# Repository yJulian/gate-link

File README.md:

# Gate Link

ESP32-S3 firmware for a two-leaf gate controller, exposed to [Home Assistant](https://www.home-assistant.io/) over MQTT with [MQTT Discovery](https://www.home-assistant.io/integrations/mqtt/#mqtt-discovery). No manual YAML entity setup needed.

`no_std` Rust on the [Embassy](https://embassy.dev/) async executor (via `esp-rtos`), targeting `xtensa-esp32s3-none-elf`.

## Features

- Open / close / stop, plus impulse control (local push button and radio
  remote) with the classic open → stop → close → stop → open press cycle
- Two independent light barriers: one stops the gate outright, the other
  only blocks closing
- Wind guard (anemometer) input that force-opens and locks the gate until
  explicitly reset (dedicated input or an MQTT button)
- Light barrier bypass (MQTT switch or local input) for faulty barriers:
  the next open/close movement ignores both barriers, then it turns itself
  off again
- Warning light that blinks while the gate moves and while the bypass is on
- Gate leaf position and wind-lock state persisted to flash, so a power
  loss doesn't lose track of where the gate was
- First-boot provisioning: the device opens its own Wi-Fi hotspot with an
  HTTP form to collect Wi-Fi + MQTT settings — no hardcoded credentials

## Hardware / wiring

GPIO assignments and input polarity are hardcoded in the wiring section at
the top of `main()` in `src/bin/main.rs`; leaf timing lives in
`src/physical/gate_config.rs`. Default pinout (ESP32-S3-DevKitC-1):

| Signal                        | GPIO |
|-------------------------------|------|
| BOOT button (config reset)    | 0    |
| Leaf A: open / close relay    | 15 / 16 |
| Leaf B: open / close relay    | 17 / 18 |
| Warning light (`LAMP_BLINK`)  | 21   |
| IN1 local push button         | 7    |
| IN2 radio remote              | 8    |
| IN3 wind sensor (anemometer)  | 9    |
| IN4 wind lock reset           | 10   |
| IN5 light barrier 1           | 11   |
| IN6 light barrier 2           | 12   |
| IN7 light barrier bypass      | 13   |

All inputs are active-low with an internal pull-up. Each leaf runs 15s per
direction by default, with leaf A opening first and leaf B closing first.

## Building

The toolchain is pinned via `rust-toolchain.toml` to the `esp` channel,
installed with [`espup`](https://github.com/esp-rs/espup). The target
(`xtensa-esp32s3-none-elf`) and `build-std` are already configured in
`.cargo/config.toml`, so no extra flags are needed:

```sh
cargo build --release              # what CI builds
cargo fmt --all -- --check
cargo clippy --all-features --workspace -- -D warnings
cargo test-core                    # host unit tests (gate-core, app-core, MQTT client)
cargo run                          # builds, flashes and opens a serial monitor via espflash
```

## First boot / provisioning

1. On first boot (or after a config reset), the device has no stored Wi-Fi
   credentials and opens an open (passwordless) hotspot named
   `mqtt-gate-setup` at `192.168.2.1`.
2. Connect to it and open `http://192.168.2.1/` to fill in the Wi-Fi SSID/
   password and MQTT broker host/port/credentials.
3. Submitting the form persists the config to flash and reboots the device
   into station mode, where it joins your Wi-Fi and connects to the broker.
4. To reprovision, hold the onboard **BOOT** button (GPIO0) for 5 seconds
   during boot — this erases the stored config and drops back into
   provisioning mode.

## Home Assistant integration

On connecting to the broker, the device publishes retained MQTT Discovery
configs for four entities:

| Entity                                               | Type          | Notes                                              |
|------------------------------------------------------|---------------|----------------------------------------------------|
| Gate (`mqtt_gate_cover`)                             | Cover         | open / close / stop, reports position              |
| Wind Monitor Input (`mqtt_gate_wind`)                | Binary sensor | on while the wind lock is engaged                  |
| Light Barrier Bypass (`mqtt_gate_barrier_bypass`)    | Switch        | ignore the light barriers for the next movement    |
| Reset Windmonitor (`mqtt_gate_reset_anemometer`)     | Button        | clears the wind lock                               |

No manual entity configuration in Home Assistant is required — they appear
automatically once the device connects.

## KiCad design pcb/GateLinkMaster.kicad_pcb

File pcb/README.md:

# GateLink PCB

KiCad hardware design for **GateLink Master**, the carrier board that hosts
an ESP32-DevKitC module and drives the two-leaf gate's four relays. This is
the board the [firmware](../README.md) runs on.

## What's on the board

- **U3** — ESP32-DevKitC module (socketed, not soldered directly)
- **K2–K5** — four SPDT relays (SANYOU SRD series, Form C), each switched
  through a transistor driver (Q2–Q5) with a flyback diode
- **J1** — 5-pin screw terminal for digital inputs (push button, radio
  remote, wind sensor, light barriers — see the firmware's input wiring)
- **J2–J5** — 3-pin screw terminals, one per relay (NO / COM / NC)
- **J6** — 2-pin screw terminal for 24V power input

Four relays map to the firmware's two motors: one open + one close relay
per gate leaf.

## Files

- `GateLinkMaster.kicad_pro` / `.kicad_sch` / `.kicad_pcb` — the KiCad
  project, schematic and board layout
- `fp-lib-table` / `sym-lib-table` — project-local footprint/symbol library
  tables (relative paths, so the project is self-contained if opened from
  this folder)
- `GateLinkMaster-backups/` — KiCad's automatic timestamped backups, kept
  out of the repo's diff history but versioned as zip snapshots
- `LICENSE` — GPLv3, applies to the hardware design files in this folder

## Opening the project

Requires [KiCad](https://www.kicad.org/) (developed against KiCad 9/10).
Open `GateLinkMaster.kicad_pro`; schematic and PCB editors will pick up the
project-local library tables automatically.

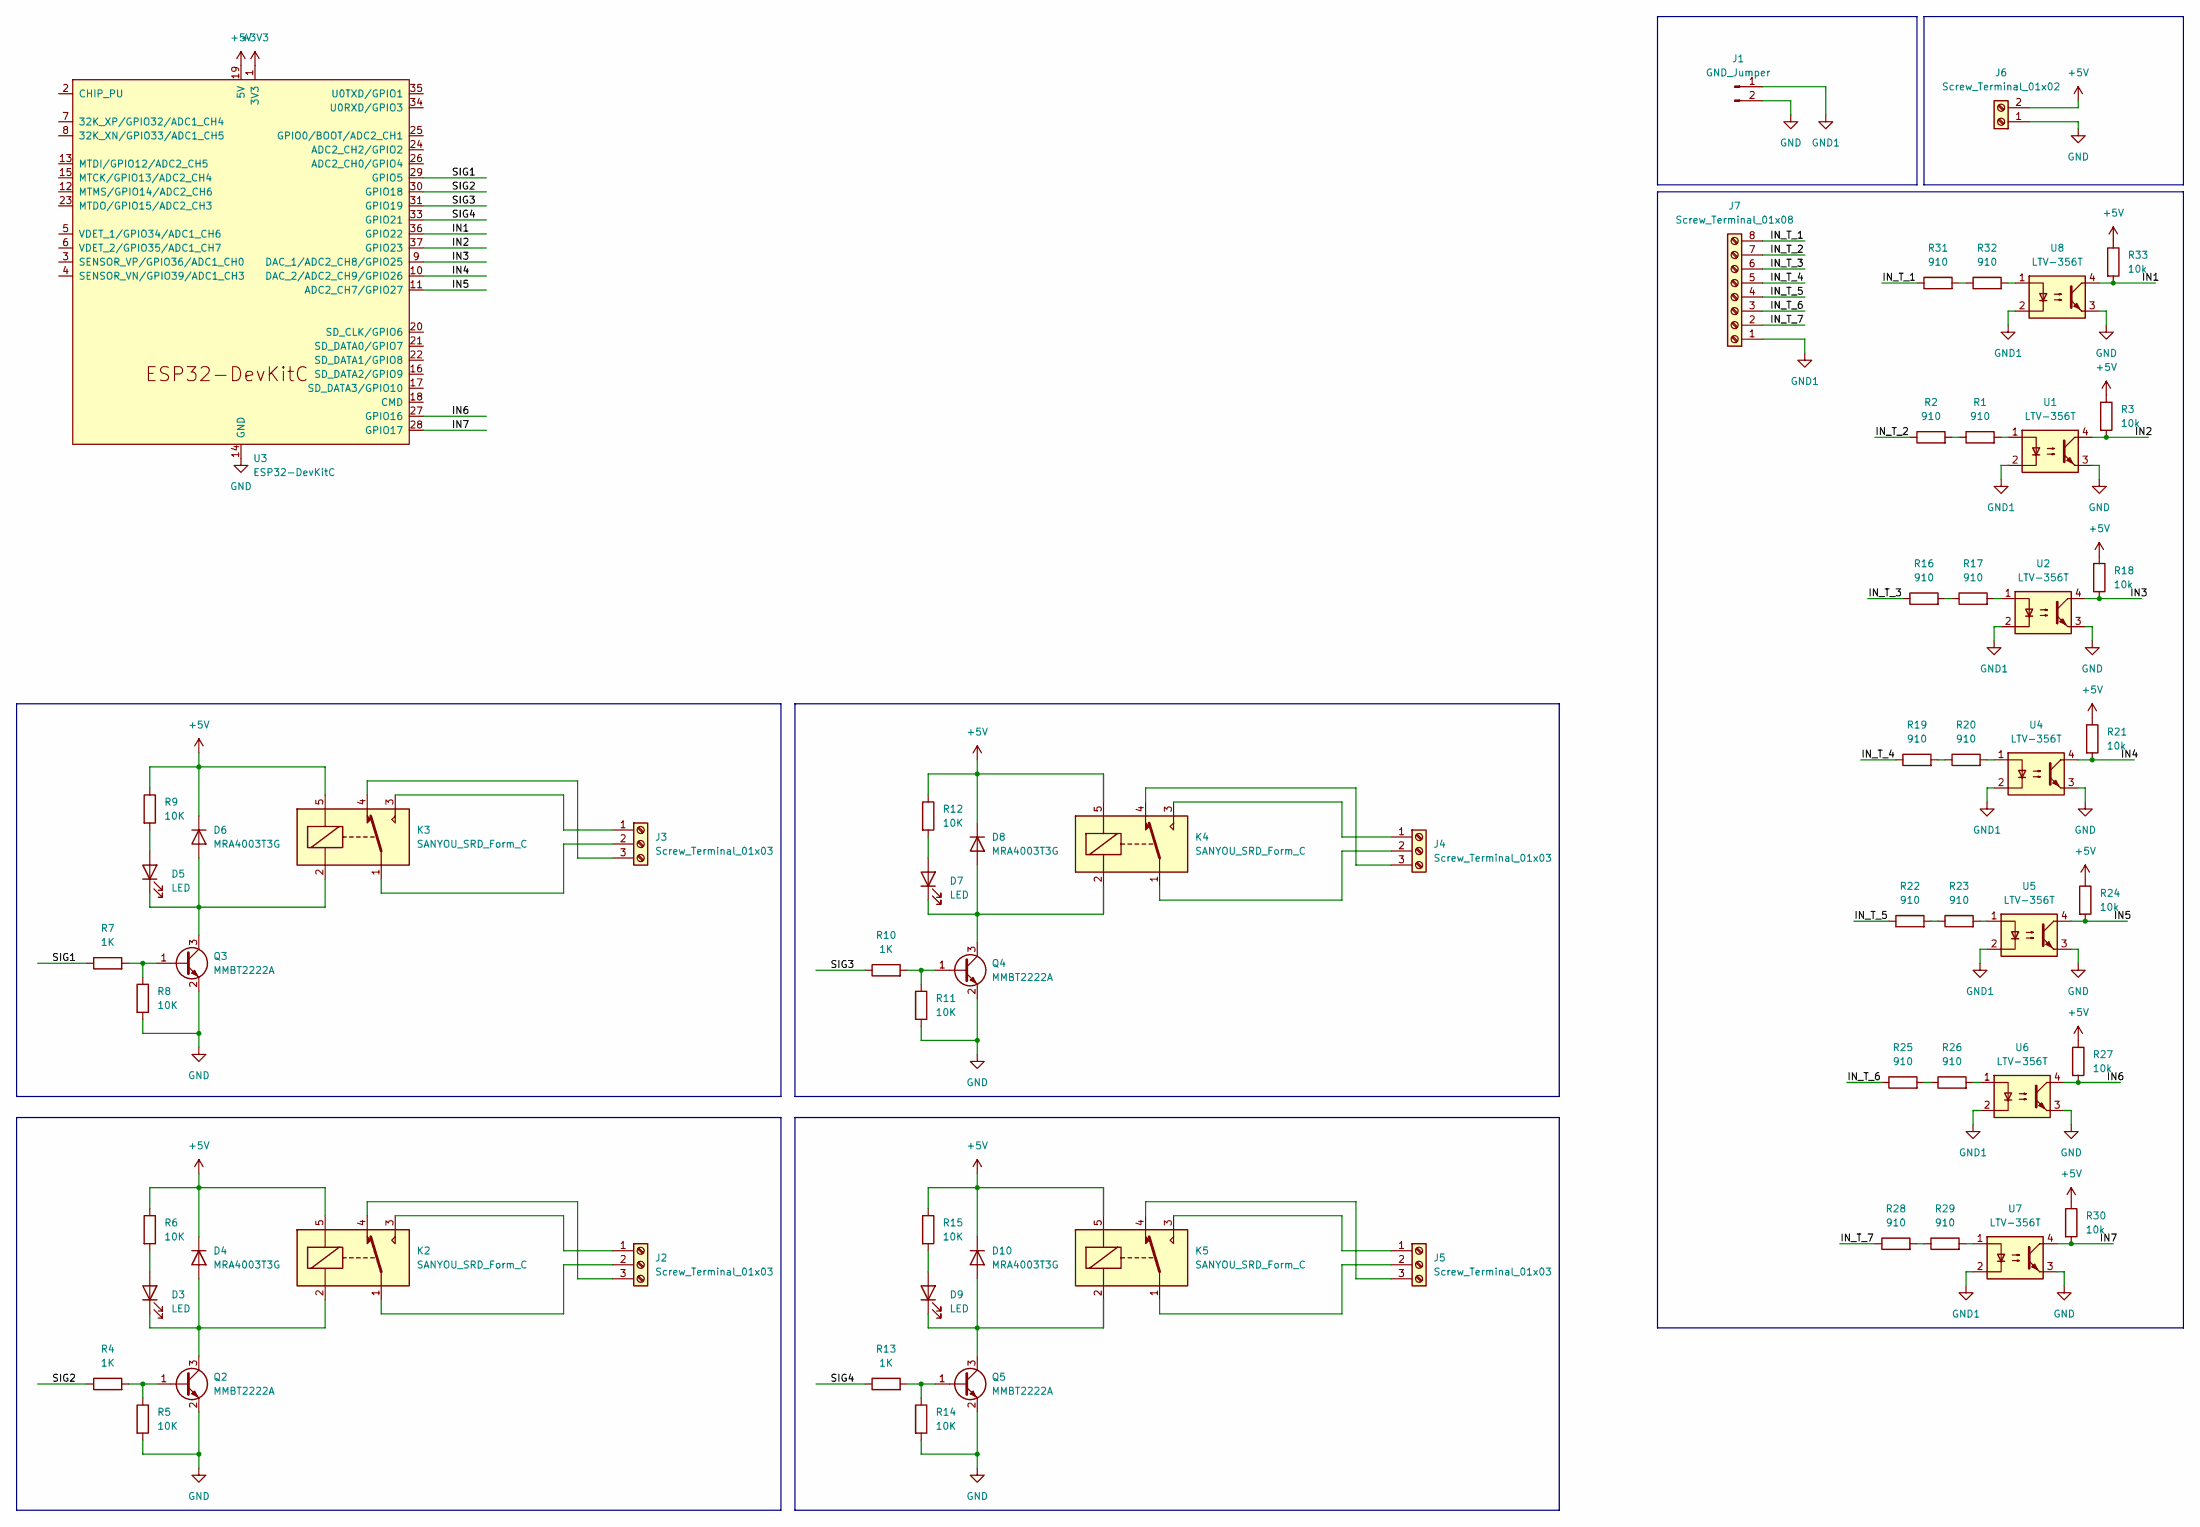
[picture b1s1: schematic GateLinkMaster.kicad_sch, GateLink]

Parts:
D3, D5, D7, D9: LED; LED_0603_1608Metric
D4, D6, D8, D10: MRA4003T3G; D_SMA
J1: GND_Jumper; PinHeader_1x02_P2.54mm_Vertical
J2, J3, J4, J5: Screw_Terminal_01x03; TerminalBlock_MaiXu_MX126-5.0-03P_1x03_P5.00mm
J6: Screw_Terminal_01x02; TerminalBlock_MaiXu_MX126-5.0-02P_1x02_P5.00mm
J7: Screw_Terminal_01x08; TerminalBlock_WAGO_236-108_1x08_P5.00mm_45Degree
K2, K3, K4, K5: SANYOU_SRD_Form_C; Relay_SPDT_SANYOU_SRD_Series_Form_C
Q2, Q3, Q4, Q5: MMBT2222A; SOT-23
R1, R2, R16, R17, R19, R20, R22, R23, R25, R26, R28, R29, R31, R32: 910; R_0805_2012Metric
R3, R18, R21, R24, R27, R30, R33: 10k; R_0805_2012Metric
R4, R7, R10, R13: 1K; R_0603_1608Metric
R5, R6, R8, R9, R11, R12, R14, R15: 10K; R_0603_1608Metric
U1, U2, U4, U5, U6, U7, U8: LTV-356T; SO-4_4.4x3.6mm_P2.54mm
U3: ESP32-DevKitC

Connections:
+3V3: U3.1 (3V3)
+5V: D4.1 (K), D6.1 (K), D8.1 (K), D10.1 (K), J6.2, K2.5, K3.5, K4.5, K5.5, R3.1, R6.1, R9.1, R12.1, R15.1, R18.1, R21.1, R24.1, R27.1, R30.1, R33.1, U3.19 (5V)
/IN1: R33.2, U3.36 (GPIO22), U8.4
/IN2: R3.2, U1.4, U3.37 (GPIO23)
/IN3: R18.2, U2.4, U3.9 (DAC_1/ADC2_CH8/GPIO25)
/IN4: R21.2, U3.10 (DAC_2/ADC2_CH9/GPIO26), U4.4
/IN5: R24.2, U3.11 (ADC2_CH7/GPIO27), U5.4
/IN6: R27.2, U3.27 (GPIO16), U6.4
/IN7: R30.2, U3.28 (GPIO17), U7.4
/IN_T_1: J7.8, R31.1
/IN_T_2: J7.7, R2.1
/IN_T_3: J7.6, R16.1
/IN_T_4: J7.5, R19.1
/IN_T_5: J7.4, R22.1
/IN_T_6: J7.3, R25.1
/IN_T_7: J7.2, R28.1
/SIG1: R7.1, U3.29 (GPIO5)
/SIG2: R4.1, U3.30 (GPIO18)
/SIG3: R10.1, U3.31 (GPIO19)
/SIG4: R13.1, U3.33 (GPIO21)
GND: J1.2, J6.1, Q2.2 (E), Q3.2 (E), Q4.2 (E), Q5.2 (E), R5.2, R8.2, R11.2, R14.2, U1.3, U2.3, U3.14 (GND), U3.32 (GND), U3.38 (GND), U4.3, U5.3, U6.3, U7.3, U8.3
GND1: J1.1, J7.1, U1.2, U2.2, U4.2, U5.2, U6.2, U7.2, U8.2
unnamed: D3.2 (A), R6.2
unnamed: D3.1 (K), D4.2 (A), K2.2, Q2.3 (C)
unnamed: D5.2 (A), R9.2
unnamed: D5.1 (K), D6.2 (A), K3.2, Q3.3 (C)
unnamed: D7.2 (A), R12.2
unnamed: D7.1 (K), D8.2 (A), K4.2, Q4.3 (C)
unnamed: D9.2 (A), R15.2
unnamed: D9.1 (K), D10.2 (A), K5.2, Q5.3 (C)
unnamed: J2.1, K2.3
unnamed: J2.2, K2.1
unnamed: J2.3, K2.4
unnamed: J3.1, K3.3
unnamed: J3.2, K3.1
unnamed: J3.3, K3.4
unnamed: J4.1, K4.3
unnamed: J4.2, K4.1
unnamed: J4.3, K4.4
unnamed: J5.1, K5.3
unnamed: J5.2, K5.1
unnamed: J5.3, K5.4
unnamed: Q2.1 (B), R4.2, R5.1
unnamed: Q3.1 (B), R7.2, R8.1
unnamed: Q4.1 (B), R10.2, R11.1
unnamed: Q5.1 (B), R13.2, R14.1
unnamed: R1.1, R2.2
unnamed: R1.2, U1.1
unnamed: R16.2, R17.1
unnamed: R17.2, U2.1
unnamed: R19.2, R20.1
unnamed: R20.2, U4.1
unnamed: R22.2, R23.1
unnamed: R23.2, U5.1
unnamed: R25.2, R26.1
unnamed: R26.2, U6.1
unnamed: R28.2, R29.1
unnamed: R29.2, U7.1
unnamed: R31.2, R32.1
unnamed: R32.2, U8.1

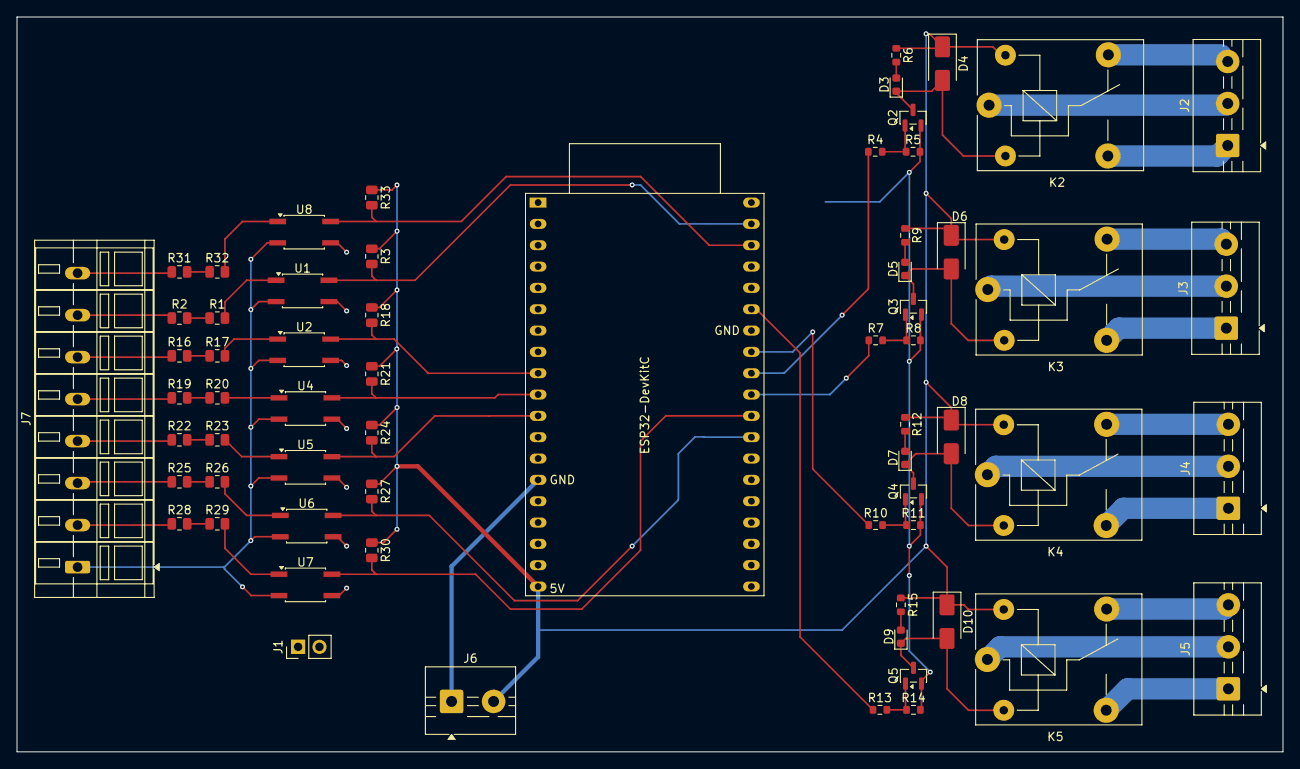
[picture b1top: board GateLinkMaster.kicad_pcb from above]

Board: 2 copper layers, 150.8 x 87.5 mm, 64 parts (0 on the bottom side), 59 nets.
